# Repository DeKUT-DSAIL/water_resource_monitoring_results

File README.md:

# water_resource-prediction_analysis
water_resource_prediction_analysis

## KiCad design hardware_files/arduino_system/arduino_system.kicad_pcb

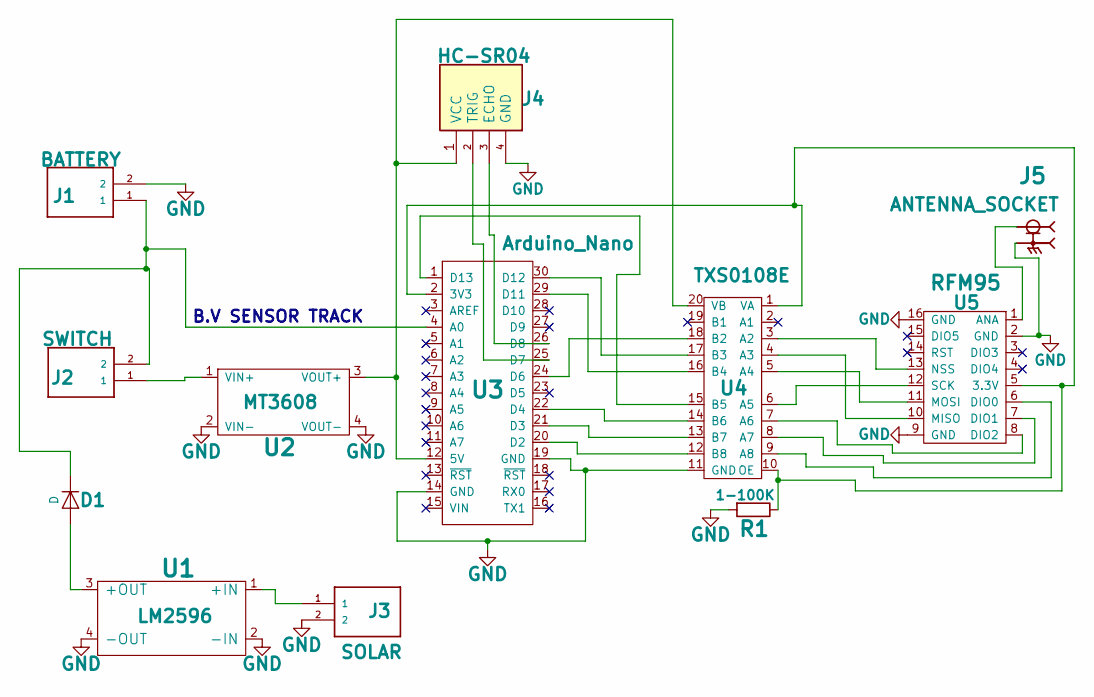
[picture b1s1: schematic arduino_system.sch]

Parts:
D1: D; D_A-405_P10.16mm_Horizontal
J1: BATTERY; TE_282815-2
J2: SWITCH; TE_282815-2
J3: SOLAR; TE_282815-2
J4: HC-SR04; TE_282836-4
J5: ANTENNA_SOCKET; SAMTEC_SMA-J-P-X-RA-TH1; PARTREV K
R1: 1-100K; R_Axial_DIN0207_L6.3mm_D2.5mm_P7.62mm_Horizontal
U1: LM2596
U2: MT3608
U3: Arduino_Nano; nano
U4: TXS0108E; SHIFT
U5: RFM95; brake1

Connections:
GND: J1.2, J3.2, J4.4 (GND), J5.2, J5.3, J5.4, J5.5, R1.2, U1.2 (-IN), U1.4 (-OUT), U2.2 (VIN-), U2.4 (VOUT-), U3.14 (GND), U3.19 (GND), U4.11 (GND), U5.2 (GND), U5.9 (GND), U5.16 (GND)
unnamed: D1.1 (K), J1.1, J2.2, U3.4 (A0)
unnamed: D1.2 (A), U1.3 (+OUT)
unnamed: J2.1, U2.1 (VIN+)
unnamed: J3.1, U1.1 (+IN)
unnamed: J4.1 (VCC), U2.3 (VOUT+), U3.12 (5V), U4.20 (VB)
unnamed: J4.2 (TRIG), U3.25 (D7)
unnamed: J4.3 (ECHO), U3.26 (D8)
unnamed: J5.1, U5.1 (ANA)
unnamed: R1.1, U3.2 (3V3), U4.1 (VA), U4.10 (OE), U5.5 (3.3V)
unnamed: U3.1 (D13), U4.15 (B5)
unnamed: U3.20 (D2), U4.12 (B8)
unnamed: U3.21 (D3), U4.13 (B7)
unnamed: U3.22 (D4), U4.14 (B6)
unnamed: U3.24 (D6), U4.18 (B2)
unnamed: U3.29 (D11), U4.16 (B4)
unnamed: U3.30 (D12), U4.17 (B3)
unnamed: U4.3 (A2), U5.13 (NSS)
unnamed: U4.4 (A3), U5.10 (MISO)
unnamed: U4.5 (A4), U5.11 (MOSI)
unnamed: U4.6 (A5), U5.12 (SCK)
unnamed: U4.7 (A6), U5.8 (DIO2)
unnamed: U4.8 (A7), U5.7 (DIO1)
unnamed: U4.9 (A8), U5.6 (DIO0)

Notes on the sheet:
B.V SENSOR TRACK

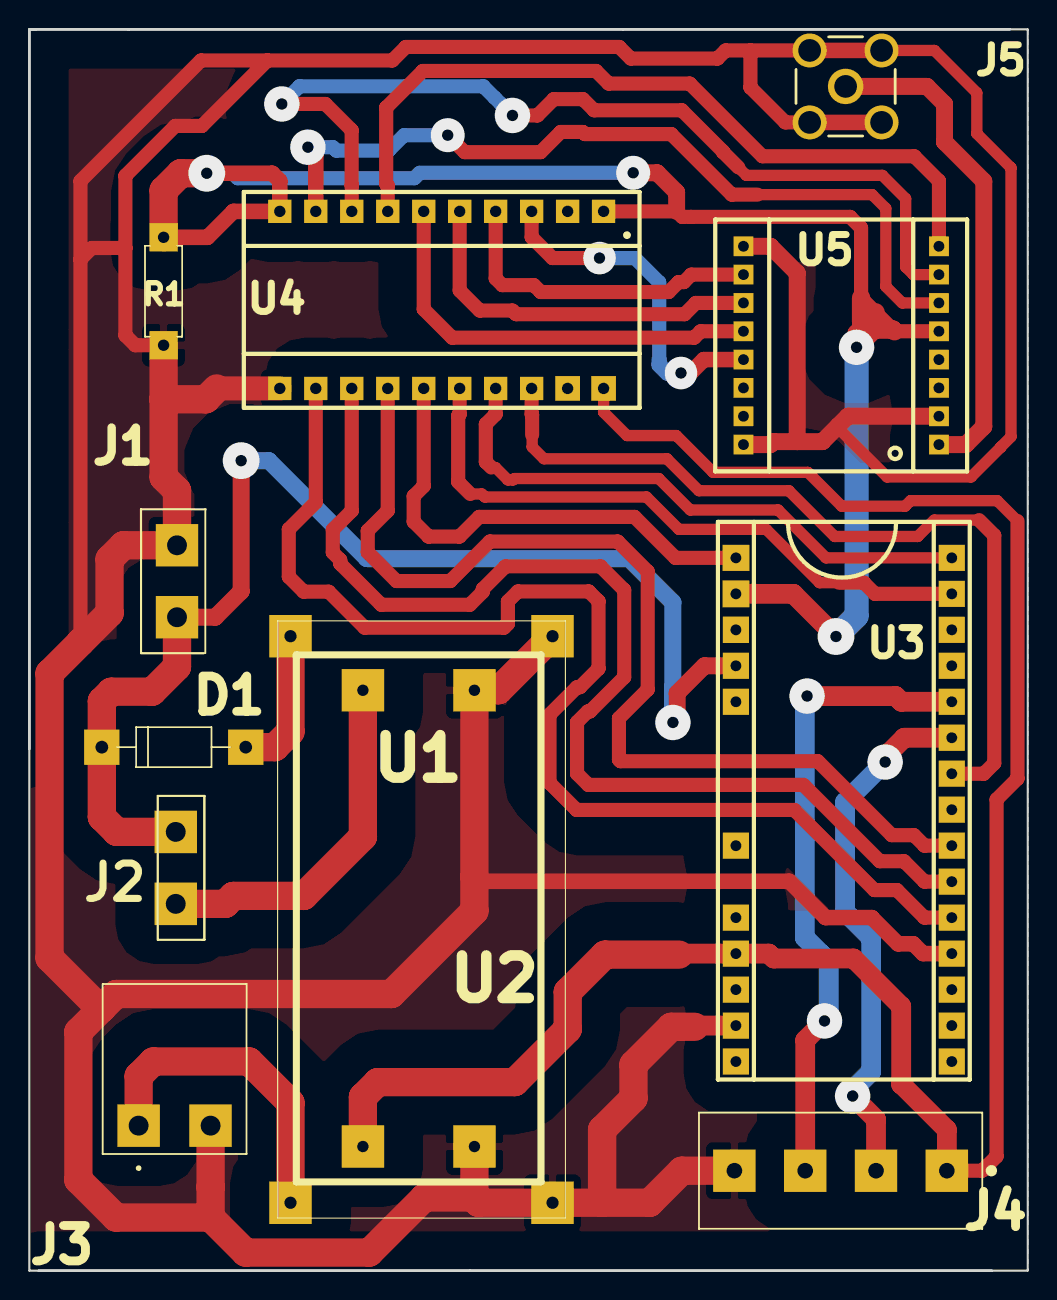
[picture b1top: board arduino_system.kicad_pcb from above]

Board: 2 copper layers, 70.5 x 87.6 mm, 12 parts (0 on the bottom side), 24 nets.

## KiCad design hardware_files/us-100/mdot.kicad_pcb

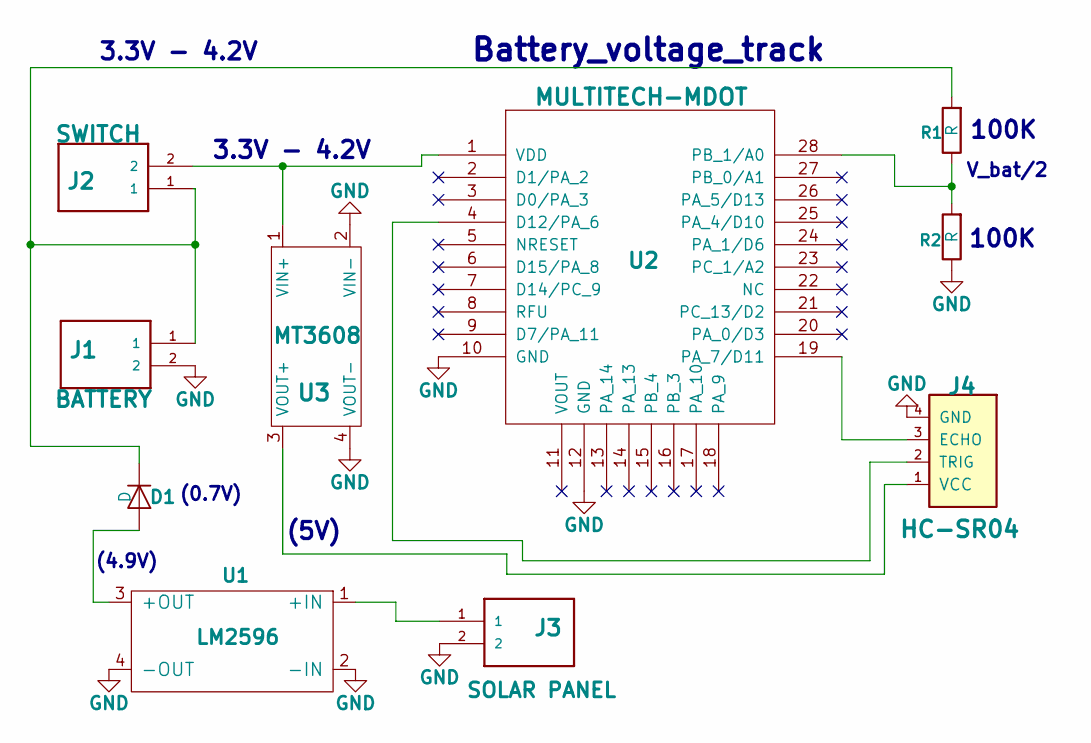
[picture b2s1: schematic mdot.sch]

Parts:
D1: D; D_A-405_P10.16mm_Horizontal
J1: BATTERY; TE_282815-2
J2: SWITCH; TE_282815-2
J3: SOLAR PANEL; TE_282815-2
J4: HC-SR04; TE_282836-4
R1, R2: R; R_Axial_DIN0207_L6.3mm_D2.5mm_P7.62mm_Horizontal
U1: LM2596
U2: MULTITECH-MDOT; MDOT_TRIAL_BAT_CHARGER
U3: MT3608

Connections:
GND: J1.2, J3.2, J4.4 (GND), R2.1, U1.2 (-IN), U1.4 (-OUT), U2.10 (GND), U2.12 (GND), U3.2 (VIN-), U3.4 (VOUT-)
unnamed: D1.1 (K), J1.1, J2.1, R1.2
unnamed: D1.2 (A), U1.3 (+OUT)
unnamed: J2.2, U2.1 (VDD), U3.1 (VIN+)
unnamed: J3.1, U1.1 (+IN)
unnamed: J4.1 (VCC), U3.3 (VOUT+)
unnamed: J4.2 (TRIG), U2.4 (D12/PA_6)
unnamed: J4.3 (ECHO), U2.19 (PA_7/D11)
unnamed: R1.1, R2.2, U2.28 (PB_1/A0)

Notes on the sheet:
V_bat/2
(0.7V)
(4.9V)
Battery_voltage_track
(5V)
3.3V - 4.2V
100K

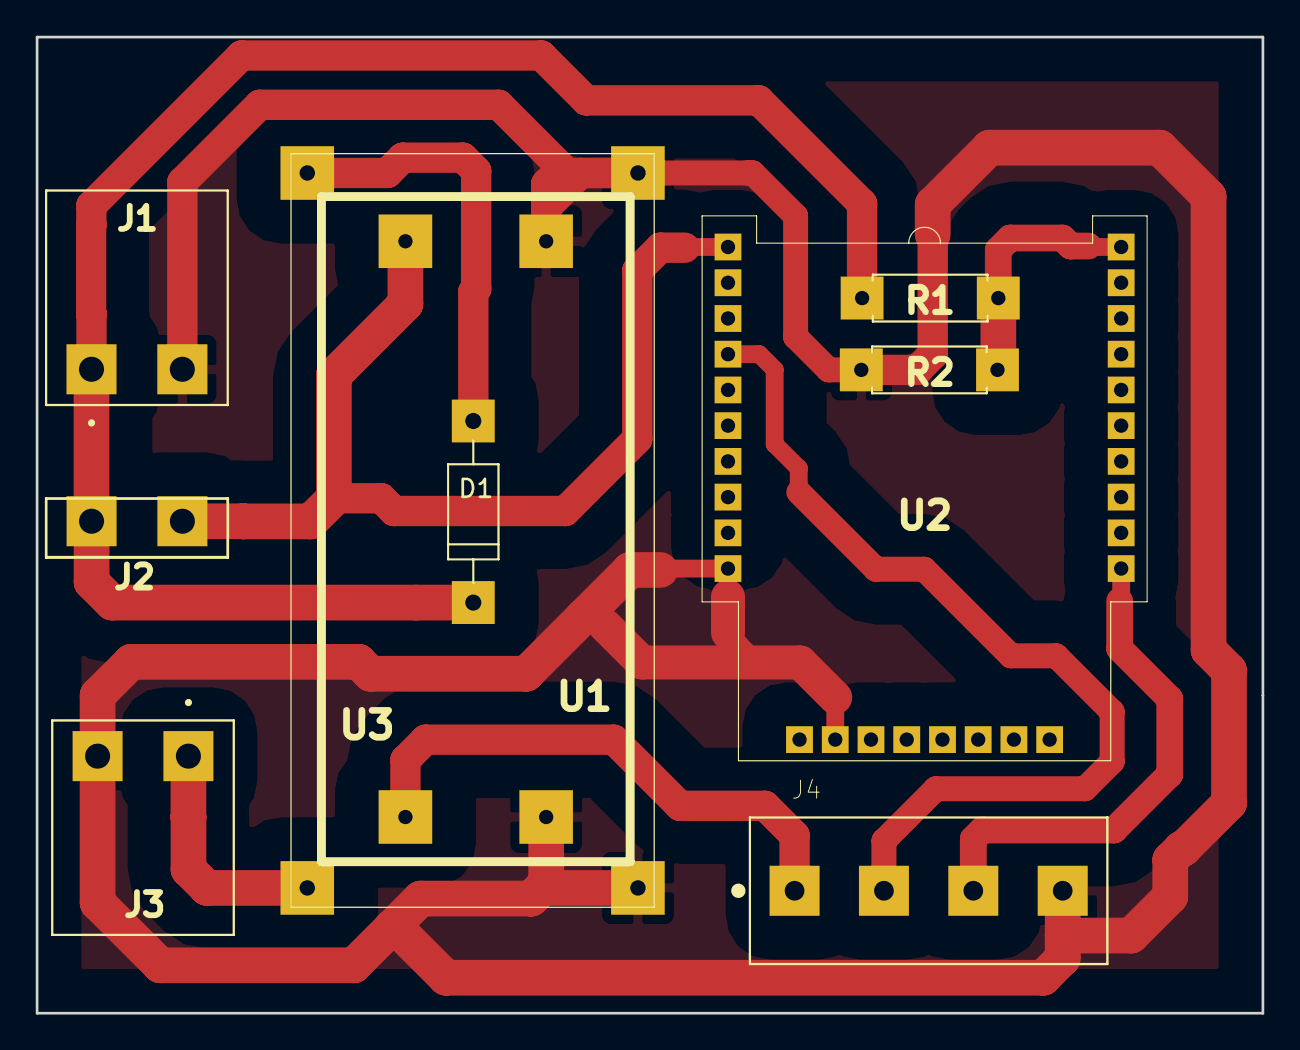
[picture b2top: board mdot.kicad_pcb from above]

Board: 2 copper layers, 68.6 x 54.6 mm, 10 parts (0 on the bottom side), 9 nets.

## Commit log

2022-10-27 multivariate_prediction_baseline+models
2022-11-03 mlp_lstm file update
2023-01-30 water resource monitoring files
